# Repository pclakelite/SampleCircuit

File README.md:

# SampleCircuit

ESP32-S3 board with NS4168 audio, CSNP1G flash, SD card.
Power chain: 24V → 12V → 5V / 3.3V (LMZM23601 buck converters).
Terminal blocks for all power rails and speaker output.

Generated with CircuitAI template system for KiCad 9.0.

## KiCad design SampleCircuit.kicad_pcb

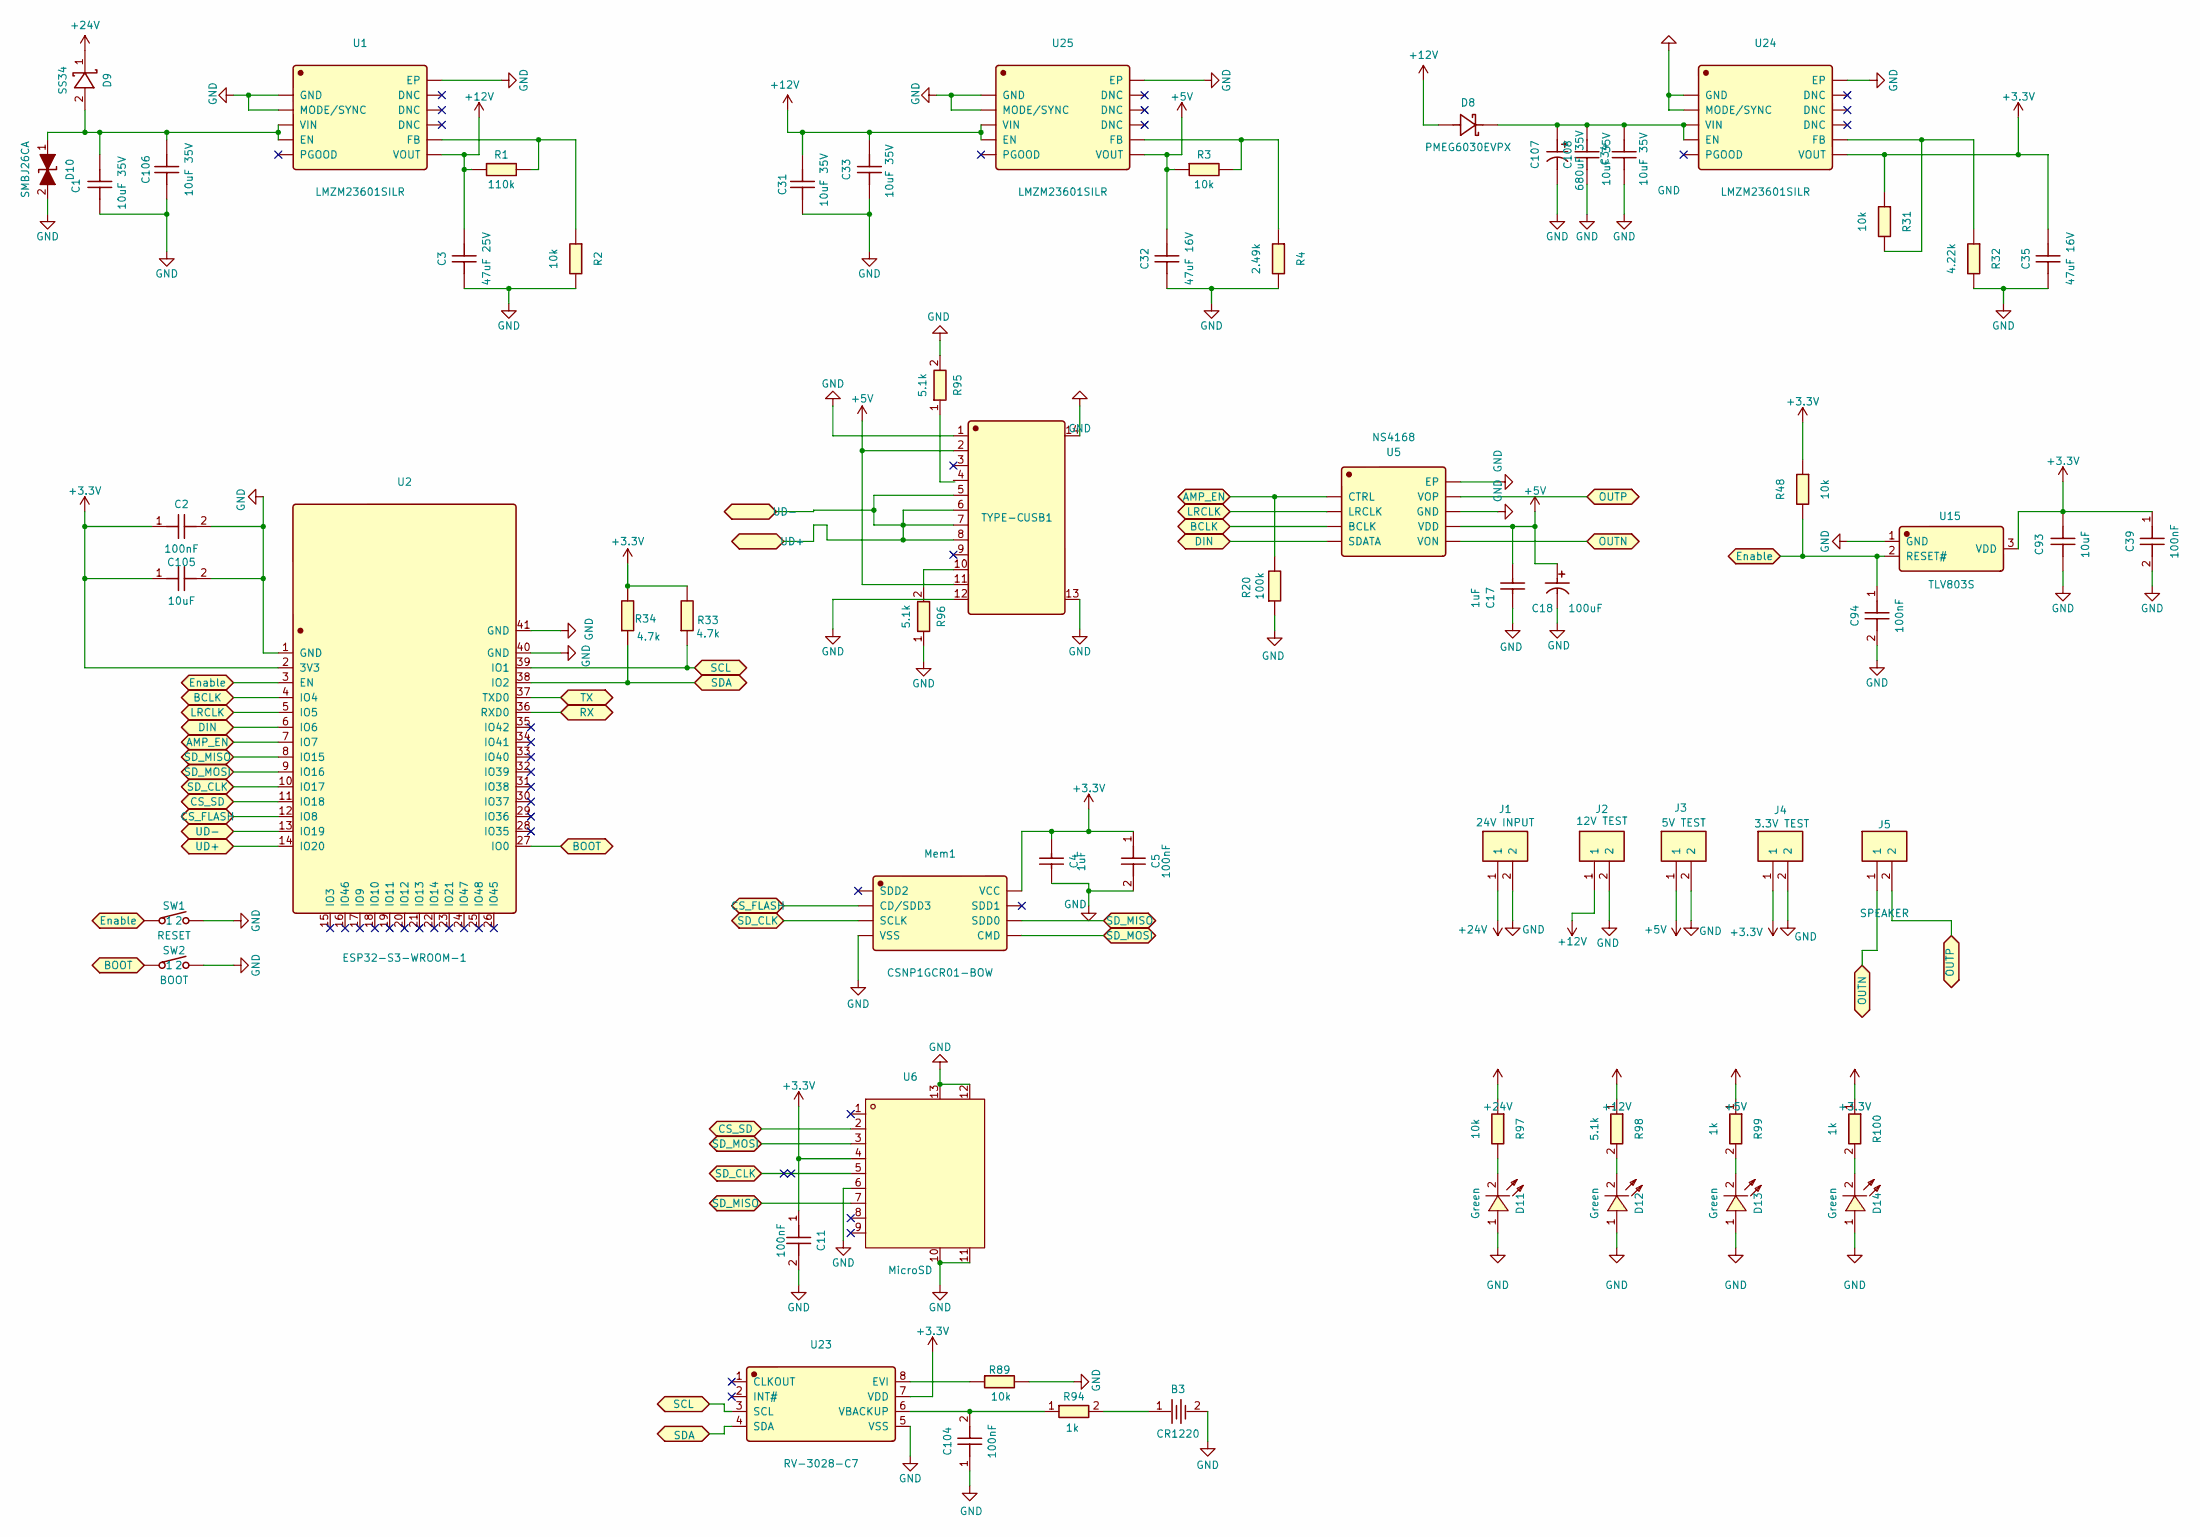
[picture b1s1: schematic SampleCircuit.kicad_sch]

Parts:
B3: CR1220; CR2032-BS-2-1; LCSC C70376
C1, C31, C33, C34, C106, C108: 10uF 35V; GRM32ER7YA106KA12L; LCSC C97973
C2, C5, C11, C39, C94, C104: 100nF; CC0805KRX7R9BB104; LCSC C49678
C3: 47uF 25V; GRM32EC81C476KE15L; LCSC C86211
C4, C17: 1uF; CL21B105KBFNNNE; LCSC C28323
C18: 100uF; HV221M025F105R; LCSC C2992088
C32: 47uF 16V; 1206X476M160NT; LCSC C172351
C35: 47uF 16V; GRM32EC81C476KE15L; LCSC C162512
C93: 10uF; GRM32ER7YA106KA12L; LCSC C97973
C105: 10uF; CL21A106KAYNNNE; LCSC C15850
C107: 680uF 35V; EEEFT1V681UP; LCSC C542257
D8: PMEG6030EVPX; LCSC C489223
D9: SS34; SS34_C8678; LCSC C8678
D10: SMBJ26CA; SMBJ26CA_C89651; LCSC C89651
D11, D12, D13, D14: Green; LED0805-R-RD; LCSC C2297
J1: 24V INPUT; WJ500V-5_08-2P-14-00A; LCSC C8465
J2: 12V TEST; WJ500V-5_08-2P-14-00A; LCSC C8465
J3: 5V TEST; WJ500V-5_08-2P-14-00A; LCSC C8465
J4: 3.3V TEST; WJ500V-5_08-2P-14-00A; LCSC C8465
J5: SPEAKER; WJ500V-5_08-2P-14-00A; LCSC C8465
Mem1: CSNP1GCR01-BOW; LCSC C2691593
R1: 110k; 0805W8F1104T5E; LCSC C17436
R2, R3, R31, R48, R89: 10k; 0805W8F1002T5E; LCSC C17414
R4: 2.49k; 0805W8F2491T5E; LCSC C21237
R20: 100k; 0805W8F1003T5E; LCSC C149504
R32: 4.22k; 0805W8F4221T5E; LCSC C17665
R33, R34: 4.7k; 0805W8F4221T5E; LCSC C17673
R94: 1k; 0805W8F1001T5E; LCSC C17513
R95, R96: 5.1k; 0805W8F5101T5E; LCSC C27834
R97: 10k; 0805W8F1002T5E
R98: 5.1k; 0805W8F5101T5E
R99, R100: 1k; 0805W8F1001T5E
SW1: RESET; TS665WS_C2686403; LCSC C2686403
SW2: BOOT; TS665WS_C2686403; LCSC C2686403
U1, U24, U25: LMZM23601SILR; LCSC C2685821
U2: ESP32-S3-WROOM-1; ESP32-S3-WROOM-1_N16R8; LCSC C2913202
U5: NS4168; NS4168_C910588; LCSC C910588
U6: MicroSD; TF-SMD_TF-PUSH; LCSC C393941
U15: TLV803S; TLV803SDBZR; LCSC C132016
U23: RV-3028-C7; RV-3028-C7_32_768KHZ_1PPM_TA_QC; LCSC C3019759
USB1: TYPE-C; TYPE-C_16PIN_2MD_073; LCSC C2765186

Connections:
+3.3V: C2.1, C4.1, C5.1, C11.1, C35.2, C39.1, C93.1, C105.1, J4.1, Mem1.8 (VCC), R31.1, R33.2, R34.2, R48.1, R100.1, U2.2 (3V3), U6.4 (VDD), U15.3 (VDD), U23.7 (VDD), U24.6 (VOUT)
+5V: C17.1, C18.1, C32.2, J3.1, R3.1, R99.1, U5.6 (VDD), U25.6 (VOUT), USB1.2 (VBUS), USB1.11 (VBUS)
+12V: C3.2, C31.2, C33.2, D8.2 (A), J2.1, R1.1, R98.1, U1.6 (VOUT), U25.3 (VIN), U25.4 (EN)
+24V: D9.1 (K), J1.1, R97.1
AMP_EN: R20.2, U2.7 (IO7), U5.1 (CTRL)
BCLK: U2.4 (IO4), U5.3 (BCLK)
BOOT: SW2.1, U2.27 (IO0)
CS_FLASH: Mem1.2 (CD/SDD3), U2.12 (IO8)
CS_SD: U2.11 (IO18), U6.2 (CD/DAT3)
DIN: U2.6 (IO6), U5.4 (SDATA)
Enable: C94.1, R48.2, SW1.1, U2.3 (EN), U15.2 (RESET#)
GND: B3.2, C1.1, C2.2, C3.1, C4.2, C5.2, C11.2, C17.2, C18.2, C31.1, C32.1, C33.1, C34.1, C35.1, C39.2, C93.2, C94.2, C104.1, C105.2, C106.1, C107.2, C108.1, D10.2 (A), D11.1 (A), D12.1 (A), D13.1 (A), D14.1 (A), J1.2, J2.2, J3.2, J4.2, Mem1.4 (VSS), R2.2, R4.2, R20.1, R32.2, R89.2, R95.2, R96.1, SW1.2, SW2.2, U1.1 (GND), U1.2 (MODE/SYNC), U1.11 (EP), U2.1 (GND), U2.40 (GND), U2.41 (GND), U5.7 (GND), U5.9 (EP), U6.6 (VSS), U6.10, U6.11, U6.12, U6.13, U15.1 (GND), U23.5 (VSS), U24.1 (GND), U24.2 (MODE/SYNC), U24.11 (EP), U25.1 (GND), U25.2 (MODE/SYNC), U25.11 (EP), USB1.1 (GND), USB1.12 (GND), USB1.13 (SHELL), USB1.14 (SHELL)
LRCLK: U2.5 (IO5), U5.2 (LRCLK)
unnamed: B3.1, R94.2
unnamed: C34.2, C107.1, C108.2, D8.1 (K), U24.3 (VIN), U24.4 (EN)
unnamed: C1.2, C106.2, D9.2 (A), D10.1 (K), U1.3 (VIN), U1.4 (EN)
unnamed: D11.2 (K), R97.2
unnamed: D12.2 (K), R98.2
unnamed: D13.2 (K), R99.2
unnamed: D14.2 (K), R100.2
unnamed: R1.2, R2.1, U1.7 (FB)
unnamed: R89.1, U23.8 (EVI)
unnamed: C104.2, R94.1, U23.6 (VBACKUP)
unnamed: R31.2, R32.1, U24.7 (FB)
unnamed: R3.2, R4.1, U25.7 (FB)
unnamed: R96.2, USB1.10 (CC2)
OUTN: J5.1, U5.5 (VON)
OUTP: J5.2, U5.8 (VOP)
RX: U2.36 (RXD0)
SCL: R33.1, U2.39 (IO1), U23.3 (SCL)
SDA: R34.1, U2.38 (IO2), U23.4 (SDA)
SD_CLK: Mem1.3 (SCLK), U2.10 (IO17), U6.5 (CLX)
SD_MISO: Mem1.6 (SDD0), U2.8 (IO15), U6.7 (DAT0)
SD_MOSI: Mem1.5 (CMD), U2.9 (IO16), U6.3 (CMD)
TX: U2.37 (TXD0)
UD+: U2.13 (IO19), U2.14 (IO20), USB1.5 (DN2), USB1.6 (DP1), USB1.7 (DN1), USB1.8 (DP2)

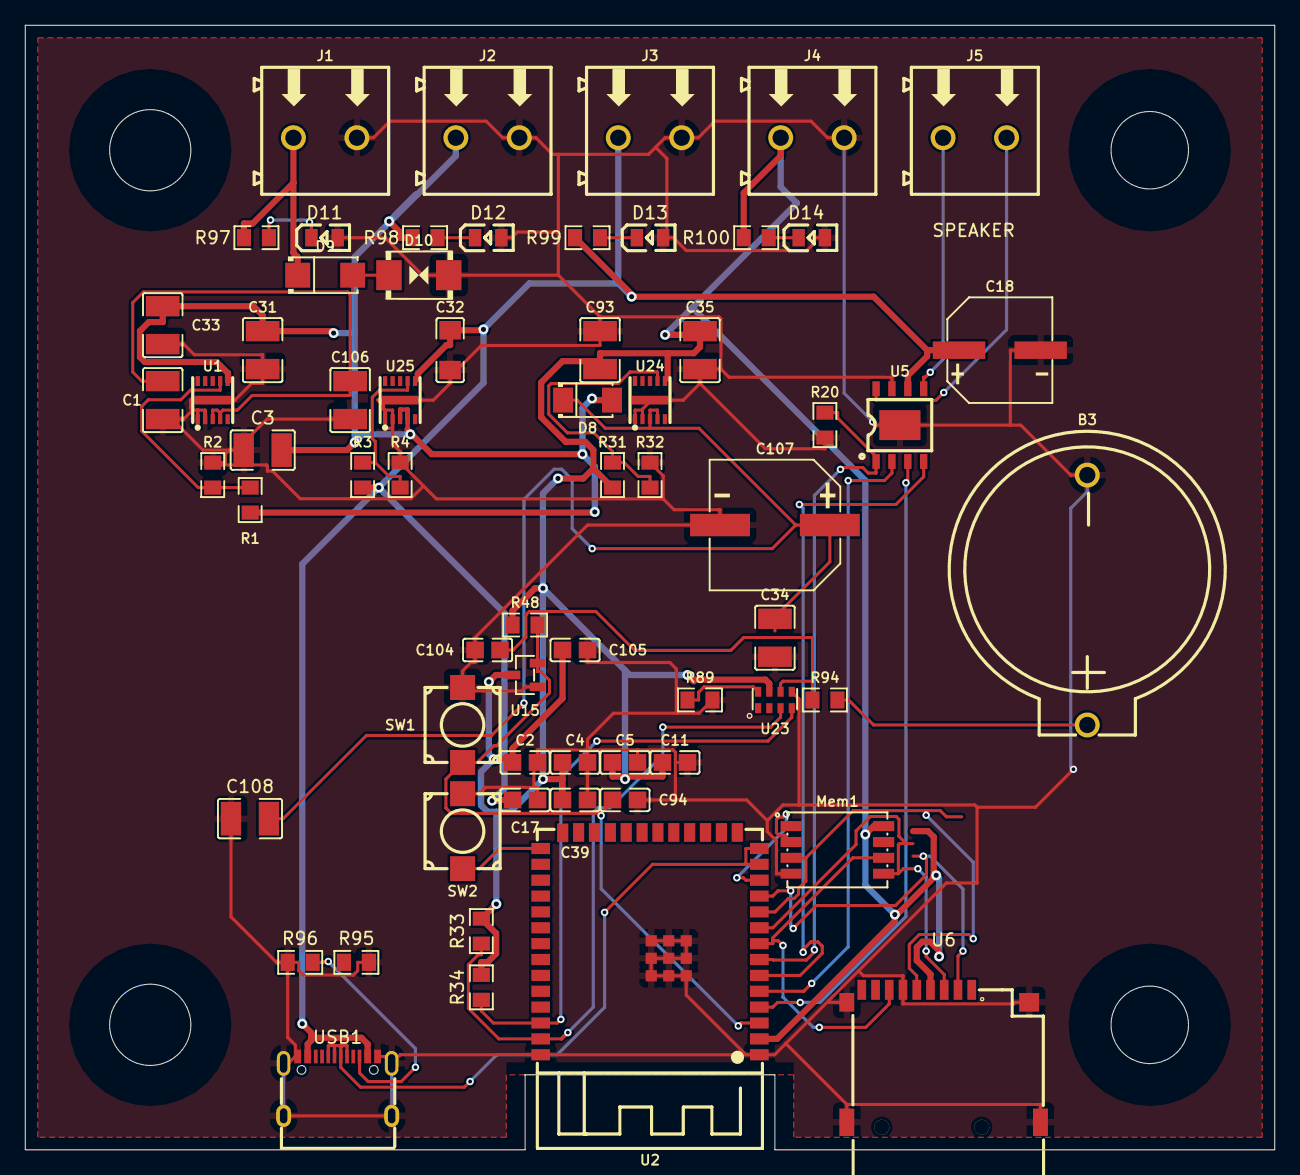
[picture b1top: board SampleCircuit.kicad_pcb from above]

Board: 2 copper layers, 100.0 x 90.0 mm, 64 parts (0 on the bottom side), 34 nets.

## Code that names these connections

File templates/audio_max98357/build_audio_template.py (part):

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Matches human-reviewed schematic v3.0:
  R7=100k GAIN_SLOT→GND (6dB), R6=1M SD_MODE→+5V (L/2+R/2 mixed), +5V rail.
  I2S ports (BCLK, LRCLK) on right side (angle=180).
  DIN port on left-top (angle=0), routes vertically down to pin 1.

Pin endpoint formula (VERIFIED):
  The (at x y) in a KiCad lib_symbol pin definition IS the wire connection point.
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
# Pin endpoints: endpoint = (sym_x + pin_at_x, sym_y - pin_at_y)
U4_PINS = {
    'DIN':       (round(U4_X - 16.51, 2), round(U4_Y - 8.89, 2)),   # pin 1  = (137.16, 92.71)
    'GAIN_SLOT': (round(U4_X - 16.51, 2), round(U4_Y - 6.35, 2)),   # pin 2  = (137.16, 95.25)
    'GND_3':     (round(U4_X - 16.51, 2), round(U4_Y - 3.81, 2)),   # pin 3  = (137.16, 97.79)
    'SD_MODE':   (round(U4_X - 16.51, 2), round(U4_Y - 1.27, 2)),   # pin 4  = (137.16, 100.33)
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    'NC_6':      (round(U4_X - 16.51, 2), round(U4_Y + 3.81, 2)),   # pin 6  = (137.16, 105.41)
    'VDD_7':     (round(U4_X - 16.51, 2), round(U4_Y + 6.35, 2)),   # pin 7  = (137.16, 107.95)
    'VDD_8':     (round(U4_X - 16.51, 2), round(U4_Y + 8.89, 2)),   # pin 8  = (137.16, 110.49)
    'OUTP':      (round(U4_X + 16.51, 2), round(U4_Y + 8.89, 2)),   # pin 9  = (170.18, 110.49)
    'OUTN':      (round(U4_X + 16.51, 2), round(U4_Y + 6.35, 2)),   # pin 10 = (170.18, 107.95)
    'GND_11':    (round(U4_X + 16.51, 2), round(U4_Y + 3.81, 2)),   # pin 11 = (170.18, 105.41)
    'NC_12':     (round(U4_X + 16.51, 2), round(U4_Y - 1.27, 2)),   # pin 12 = (170.18, 100.33)
    'NC_13':     (round(U4_X + 16.51, 2), round(U4_Y + 1.27, 2)),   # pin 13 = (170.18, 102.87)
    'LRCLK':     (round(U4_X + 16.51, 2), round(U4_Y - 3.81, 2)),   # pin 14 = (170.18, 97.79)
    'GND_15':    (round(U4_X + 16.51, 2), round(U4_Y - 6.35, 2)),   # pin 15 = (170.18, 95.25)
    'BCLK':      (round(U4_X + 16.51, 2), round(U4_Y - 8.89, 2)),   # pin 16 = (170.18, 92.71)
    'EP':        (round(U4_X, 2),          round(U4_Y + 13.97, 2)),  # pin 17 = (153.67, 115.57)
}

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
    wires = []

    # --- DIN: port → horizontal → vertical down → pin 1 ---
    wires.append(wire(DIN_PIN_X, DIN_PORT_Y,
                      U4_PINS['DIN'][0], DIN_PORT_Y))         # horizontal
    wires.append(wire(U4_PINS['DIN'][0], DIN_PORT_Y,
                      U4_PINS['DIN'][0], U4_PINS['DIN'][1]))  # vertical down

    # --- BCLK: pin 16 → horizontal → jog up → port ---
    wires.append(wire(U4_PINS['BCLK'][0], U4_PINS['BCLK'][1],
                      BCLK_JOG_X, U4_PINS['BCLK'][1]))        # horizontal
    wires.append(wire(BCLK_JOG_X, U4_PINS['BCLK'][1],
                      BCLK_JOG_X, BCLK_PORT_Y))               # vertical jog
    wires.append(wire(BCLK_JOG_X, BCLK_PORT_Y,
                      BCLK_PIN_X, BCLK_PORT_Y))               # horizontal to port

    # --- LRCLK: pin 14 → straight horizontal → port ---
    wires.append(wire(U4_PINS['LRCLK'][0], U4_PINS['LRCLK'][1],
                      LRCLK_PIN_X, LRCLK_PORT_Y))

    # --- OUTP: pin 9 → vertical jog → horizontal → port ---
    wires.append(wire(U4_PINS['OUTP'][0], U4_PINS['OUTP'][1],
                      U4_PINS['OUTP'][0], OUTP_PORT_Y))       # vertical jog
    wires.append(wire(U4_PINS['OUTP'][0], OUTP_PORT_Y,
                      OUTP_PIN_X, OUTP_PORT_Y))               # horizontal to port

    # --- OUTN: pin 10 → straight horizontal → port ---
    wires.append(wire(U4_PINS['OUTN'][0], U4_PINS['OUTN'][1],
                      OUTN_PIN_X, OUTN_PORT_Y))

    # --- R7: GAIN_SLOT to GND ---
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
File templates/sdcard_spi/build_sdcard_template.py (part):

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# U6 pin endpoints (Micro_SD_Card_C585354, angle=0)
U6_PINS = {
    'DAT2':    (round(U6_X - 22.86, 2), round(U6_Y - 7.62, 2)),   # pin 1 NC
    'DAT3_CD': (round(U6_X - 22.86, 2), round(U6_Y - 5.08, 2)),   # pin 2 CS_SD
    'CMD':     (round(U6_X - 22.86, 2), round(U6_Y - 2.54, 2)),   # pin 3 SD_MOSI
    'VDD':     (round(U6_X - 22.86, 2), round(U6_Y, 2)),           # pin 4 +3.3V
    'CLK':     (round(U6_X - 22.86, 2), round(U6_Y + 2.54, 2)),   # pin 5 SD_CLK
    'VSS':     (round(U6_X - 22.86, 2), round(U6_Y + 5.08, 2)),   # pin 6 GND
    'DAT0':    (round(U6_X - 22.86, 2), round(U6_Y + 7.62, 2)),   # pin 7 SD_MISO
    'DAT1':    (round(U6_X - 22.86, 2), round(U6_Y + 10.16, 2)),  # pin 8 NC
    'SHIELD':  (round(U6_X + 20.32, 2), round(U6_Y + 15.24, 2)),  # pin 9 GND
}
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                                   val_pos=(gx, round(gy + 3.81, 2))))

    # Port symbols
    symbols.append(make_port("#PORT01", "Ports:CS_SD", "CS_SD", PORT_X, U6_PINS['DAT3_CD'][1]))
    symbols.append(make_port("#PORT02", "Ports:SD_MOSI", "SD_MOSI", PORT_X, U6_PINS['CMD'][1]))
    symbols.append(make_port("#PORT03", "Ports:SD_CLK", "SD_CLK", PORT_X, U6_PINS['CLK'][1]))
    symbols.append(make_port("#PORT04", "Ports:SD_MISO", "SD_MISO", PORT_X, U6_PINS['DAT0'][1]))

    symbols_str = "\n\n".join(symbols)

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    wires_raw = []

    # Port → pin wires (horizontal, same Y)
    # CS_SD port → DAT3/CD pin
    wires_raw.append(wire(PORT_PIN_X, U6_PINS['DAT3_CD'][1],
                          U6_PINS['DAT3_CD'][0], U6_PINS['DAT3_CD'][1]))
    # SD_MOSI port → CMD pin
    wires_raw.append(wire(PORT_PIN_X, U6_PINS['CMD'][1],
                          U6_PINS['CMD'][0], U6_PINS['CMD'][1]))
    # SD_CLK port → CLK pin
    wires_raw.append(wire(PORT_PIN_X, U6_PINS['CLK'][1],
                          U6_PINS['CLK'][0], U6_PINS['CLK'][1]))
    # SD_MISO port → DAT0 pin
    wires_raw.append(wire(PORT_PIN_X, U6_PINS['DAT0'][1],
                          U6_PINS['DAT0'][0], U6_PINS['DAT0'][1]))

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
